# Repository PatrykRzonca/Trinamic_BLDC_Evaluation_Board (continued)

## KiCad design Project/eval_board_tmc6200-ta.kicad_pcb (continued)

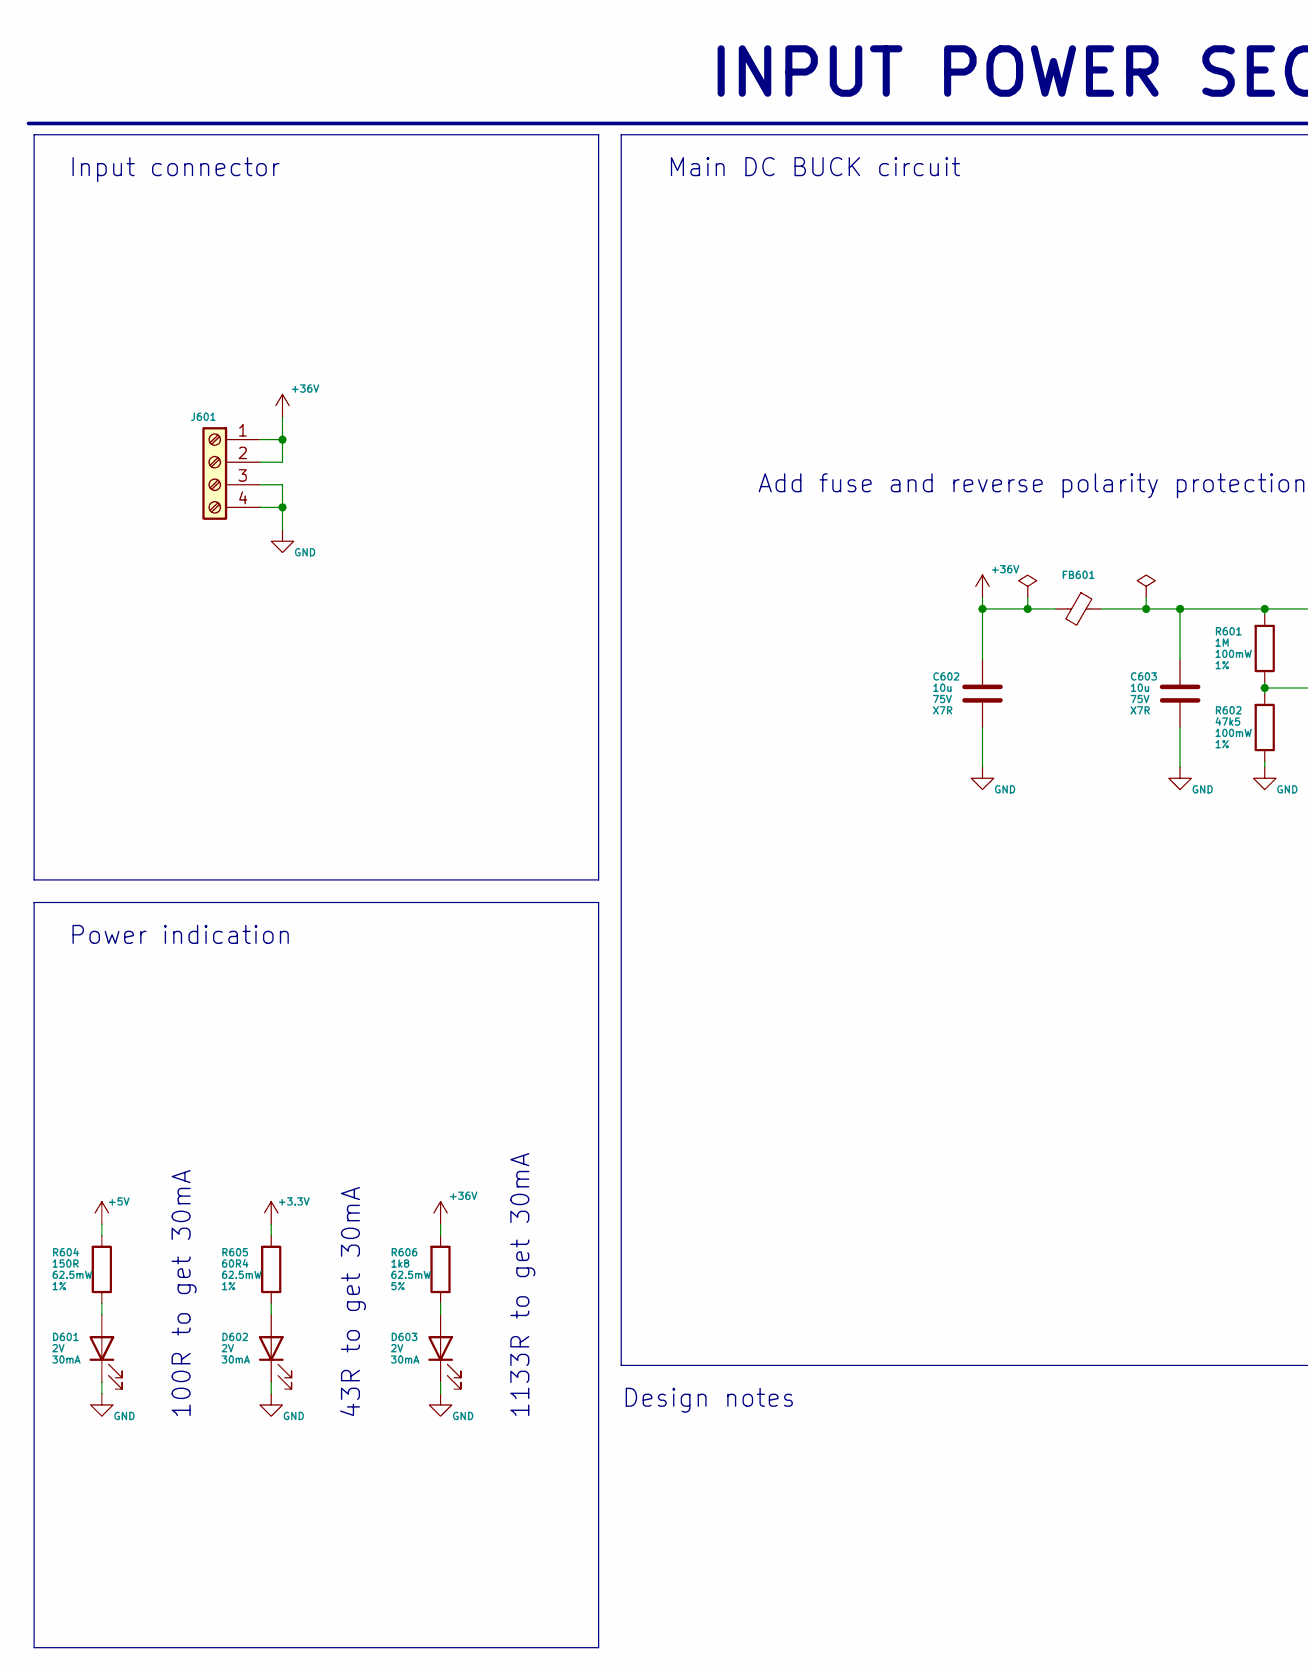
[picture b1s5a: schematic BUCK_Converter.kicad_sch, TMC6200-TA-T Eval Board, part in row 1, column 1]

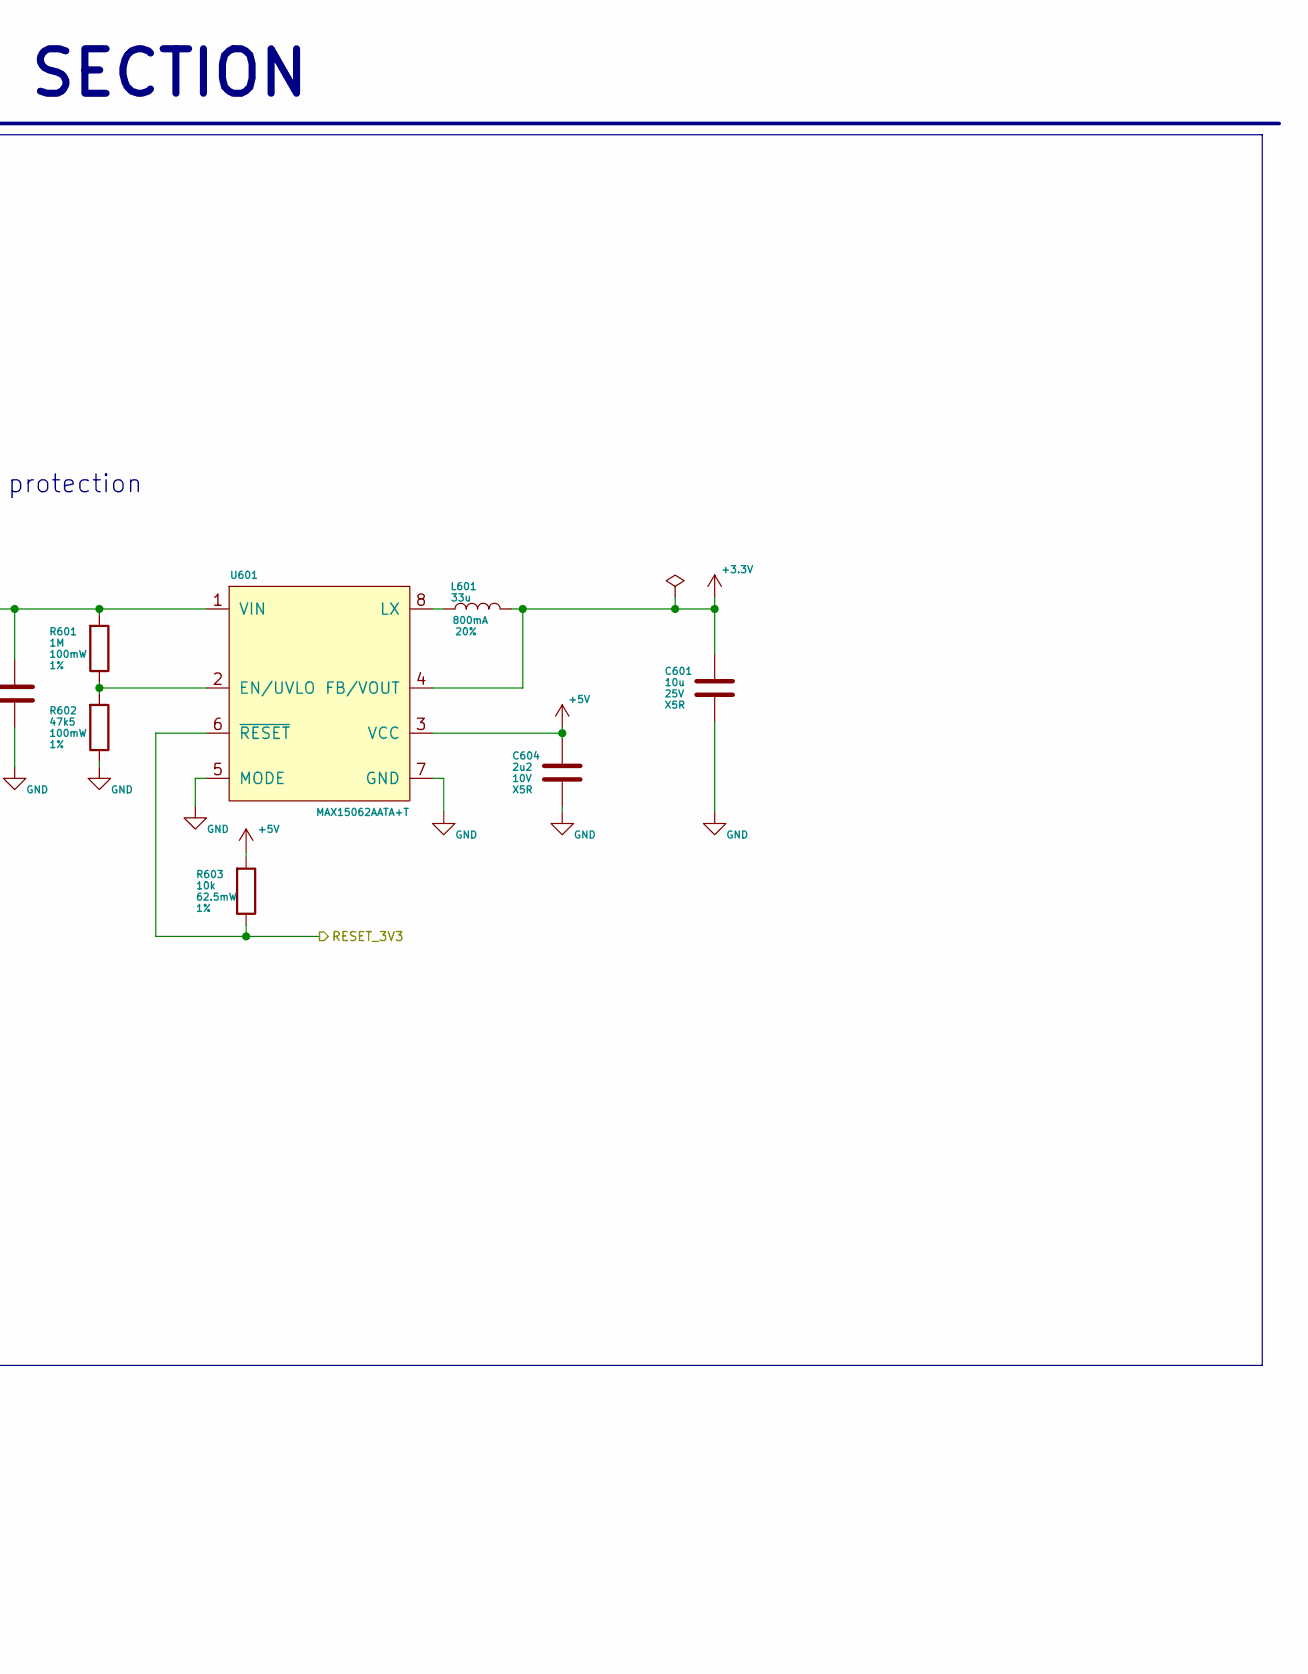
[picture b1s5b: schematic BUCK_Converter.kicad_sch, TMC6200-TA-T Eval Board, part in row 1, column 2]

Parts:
C601: 10u; C_1206_3216Metric; DC Voltage 25V; Tolerance 20%; Part Number CL31A106KAHNNNE
C602, C603: 10u; C_1210_3225Metric; DC Voltage 75V; Tolerance 10%; Part Number C3225X7R1N106K250AC
C604: 2u2; C_0603_1608Metric; DC Voltage 10V; Tolerance 10%; Part Number LMK107BJ225KAHT
D601, D602, D603: LED; D_0402_1005Metric; Forward Voltage 2V; Part Number 150040VS73240
FB601: Ferrite_Bead; R_0603_1608Metric
J601: Screw_Terminal_01x04; PinSocket_1x04_P2.54mm_Vertical
L601: 33u; L_Coilcraft_XAL5030; Tolerance 20%
R601: 1M; R_0603_1608Metric; Tolerance 1%; Voltage 75V; Part Number CRCW06031M00FKEAC
R602: 47k5; R_0603_1608Metric; Tolerance 1%; Voltage 75V; Part Number CRCW060347K5FKEAC
R603: 10k; R_0402_1005Metric; Tolerance 1%; Voltage 50V; Part Number RC0402FR-0710KL
R604: 150R; R_0402_1005Metric; Tolerance 1%; Voltage 50V; Part Number RC0402FR-7D150RL
R605: 60R4; R_0402_1005Metric; Tolerance 1%; Voltage 50V; Part Number RC0402FR-0760R4L
R606: 1k8; R_0402_1005Metric; Tolerance 5%; Voltage 50V; Part Number RC0402JR-071K8L
U601: MAX15062AATA+T; MAX15062AATA+T_TDFN-8

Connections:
+3V3: C601.1, L601.2, R605.2, U601.4 (FB/VOUT); also elsewhere on the board
+5V: C604.1, R603.2, R604.2, U601.3 (VCC); also elsewhere on the board
+36V: C602.1, FB601.2, J601.1, J601.2, R606.2; also elsewhere on the board
/Microcontroller/RESET_3V3: R603.1, U601.6 (~RESET); also elsewhere on the board
GND: C601.2, C602.2, C603.2, C604.2, D601.1 (K), D602.1 (K), D603.1 (K), J601.3, J601.4, R602.1, U601.5 (MODE), U601.7 (GND); also elsewhere on the board
unnamed: C603.1, FB601.1, R601.2, U601.1 (VIN)
unnamed: D601.2 (A), R604.1
unnamed: D602.2 (A), R605.1
unnamed: D603.2 (A), R606.1
unnamed: L601.1, U601.8 (LX)
unnamed: R601.1, R602.2, U601.2 (EN/UVLO)

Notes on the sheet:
1133R to get 30mA
Main DC BUCK circuit
Power indication
Add fuse and reverse polarity protection
Input connector
Design notes
INPUT POWER SECTION
100R to get 30mA
43R to get 30mA

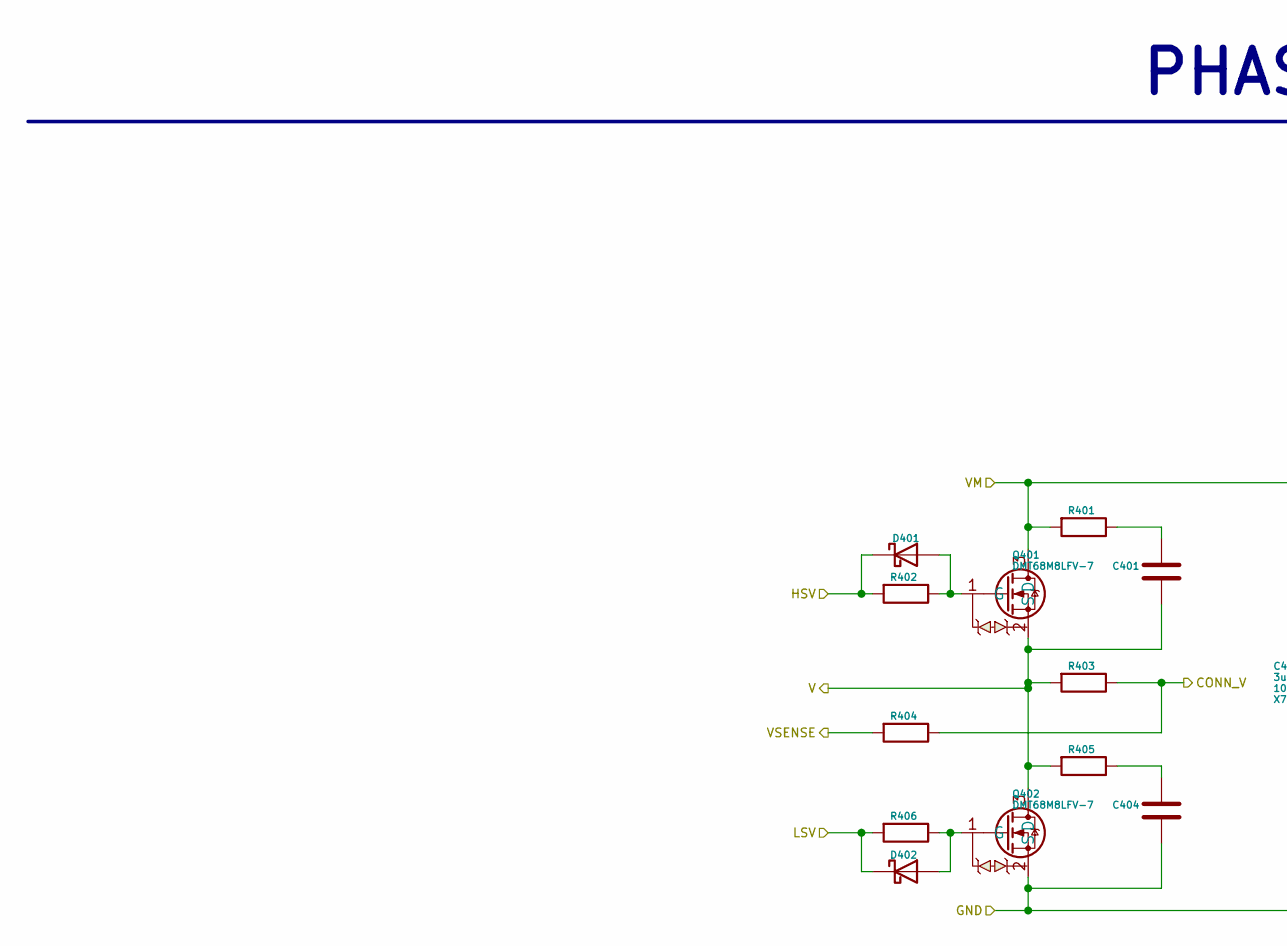
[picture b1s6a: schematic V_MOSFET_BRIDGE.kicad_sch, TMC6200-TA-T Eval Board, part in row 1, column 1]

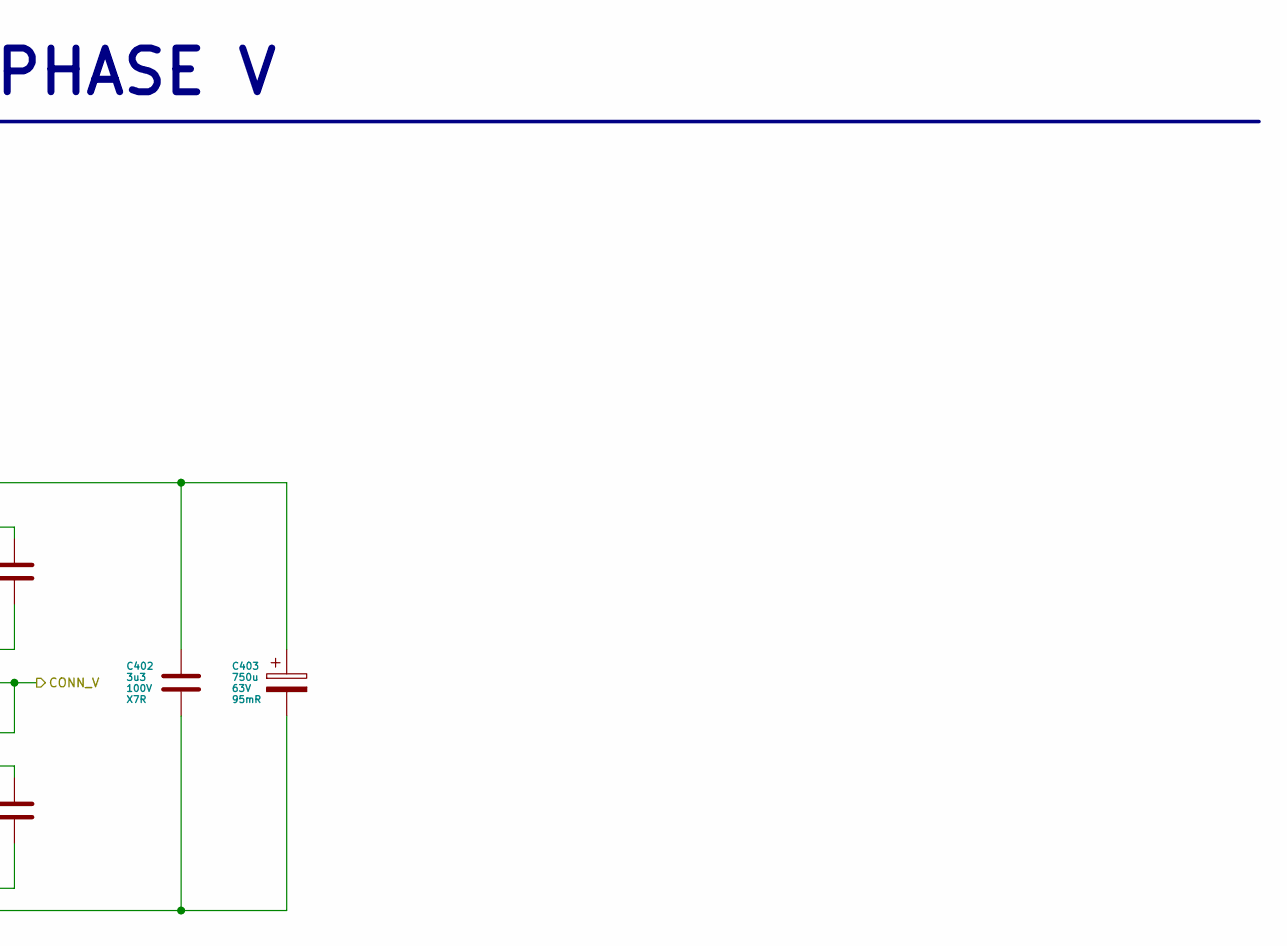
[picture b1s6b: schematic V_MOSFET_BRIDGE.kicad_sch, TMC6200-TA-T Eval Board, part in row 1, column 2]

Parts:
C401, C404: C; C_0402_1005Metric
C402: 3u3; C_1812_4532Metric; DC Voltage 100V; Tolerance 10%; Part Number C1812C335K1RACTU
C403: 750u; CP_Elec_18x17.5; DC Voltage 63V; Tolerance 20%; Part Number EEE-TP1J751V
D401, D402: D_Schottky; D_SOD-123
Q401, Q402: DMT68M8LFV-7; DMT68M8LFV-7_PowerDI5060-8
R401, R402, R404, R405, R406: R; R_0402_1005Metric
R403: R; R_1210_3225Metric

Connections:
+36V: C402.2, C403.1, Q401.3 (D), R401.2; also elsewhere on the board
/BLDC_MOTOR/CONN_V: R403.1, R404.1
/BLDC_MOTOR/HSV: D401.1 (K), R402.2; also elsewhere on the board
/BLDC_MOTOR/LSV: D402.1 (K), R406.2; also elsewhere on the board
/BLDC_MOTOR/V: C401.1, Q401.2 (S), Q402.3 (D), R403.2, R405.2; also elsewhere on the board
/BLDC_MOTOR/VSENSE: R404.2; also elsewhere on the board
GND: C402.1, C403.2, C404.1, Q402.2 (S); also elsewhere on the board
unnamed: C401.2, R401.1
unnamed: C404.2, R405.1
unnamed: D401.2 (A), Q401.1 (G), R402.1
unnamed: D402.2 (A), Q402.1 (G), R406.1

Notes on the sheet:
PHASE V

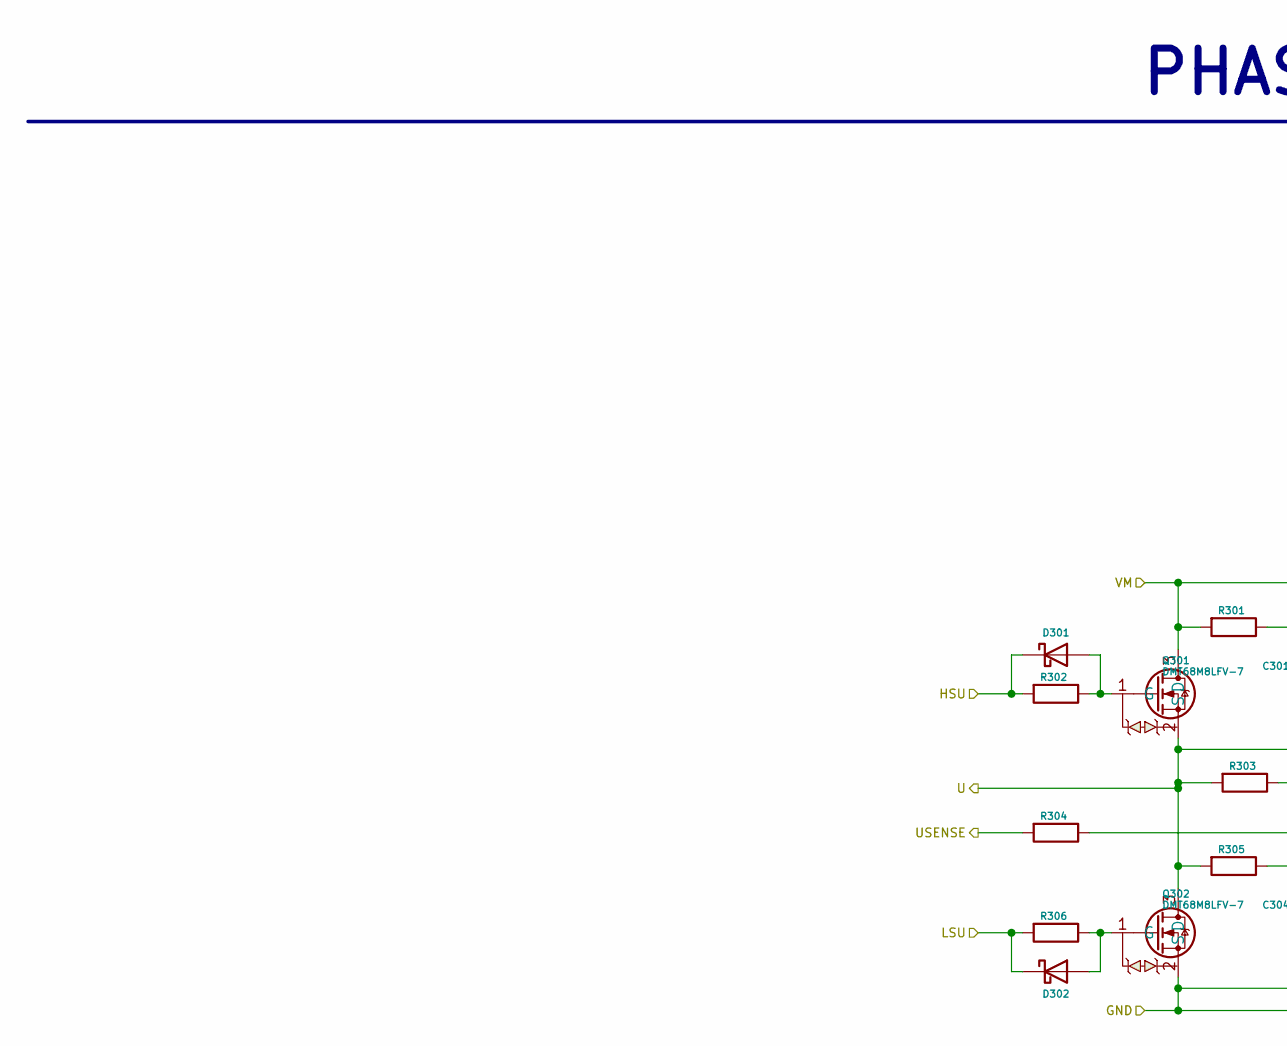
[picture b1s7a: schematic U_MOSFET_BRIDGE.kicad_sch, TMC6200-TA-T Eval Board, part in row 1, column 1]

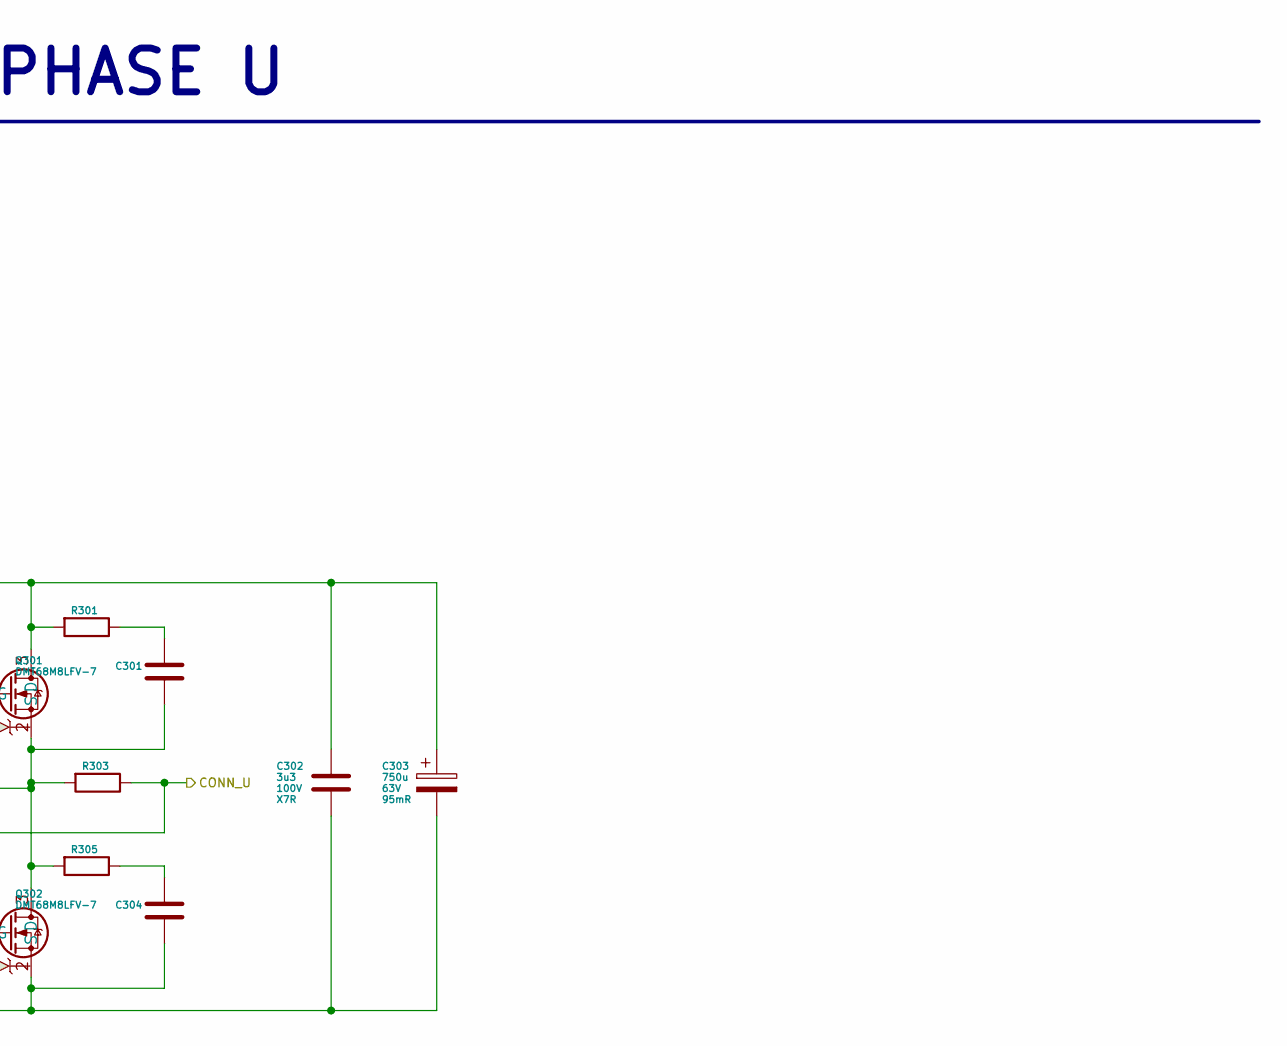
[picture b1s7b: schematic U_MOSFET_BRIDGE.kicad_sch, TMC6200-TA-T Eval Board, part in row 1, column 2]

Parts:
C301, C304: C; C_0402_1005Metric
C302: 3u3; C_1812_4532Metric; DC Voltage 100V; Tolerance 10%; Part Number C1812C335K1RACTU
C303: 750u; CP_Elec_18x17.5; DC Voltage 63V; Tolerance 20%; Part Number EEE-TP1J751V
D301, D302: D_Schottky; D_SOD-123
Q301, Q302: DMT68M8LFV-7; DMT68M8LFV-7_PowerDI5060-8
R301, R302, R304, R305, R306: R; R_0402_1005Metric
R303: R; R_1210_3225Metric

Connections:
+36V: C302.2, C303.1, Q301.3 (D), R301.2; also elsewhere on the board
/BLDC_MOTOR/CONN_U: R303.1, R304.1
/BLDC_MOTOR/HSU: D301.1 (K), R302.2; also elsewhere on the board
/BLDC_MOTOR/LSU: D302.1 (K), R306.2; also elsewhere on the board
/BLDC_MOTOR/U: C301.1, Q301.2 (S), Q302.3 (D), R303.2, R305.2; also elsewhere on the board
/BLDC_MOTOR/USENSE: R304.2; also elsewhere on the board
GND: C302.1, C303.2, C304.1, Q302.2 (S); also elsewhere on the board
unnamed: C301.2, R301.1
unnamed: C304.2, R305.1
unnamed: D301.2 (A), Q301.1 (G), R302.1
unnamed: D302.2 (A), Q302.1 (G), R306.1

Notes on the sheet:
PHASE U

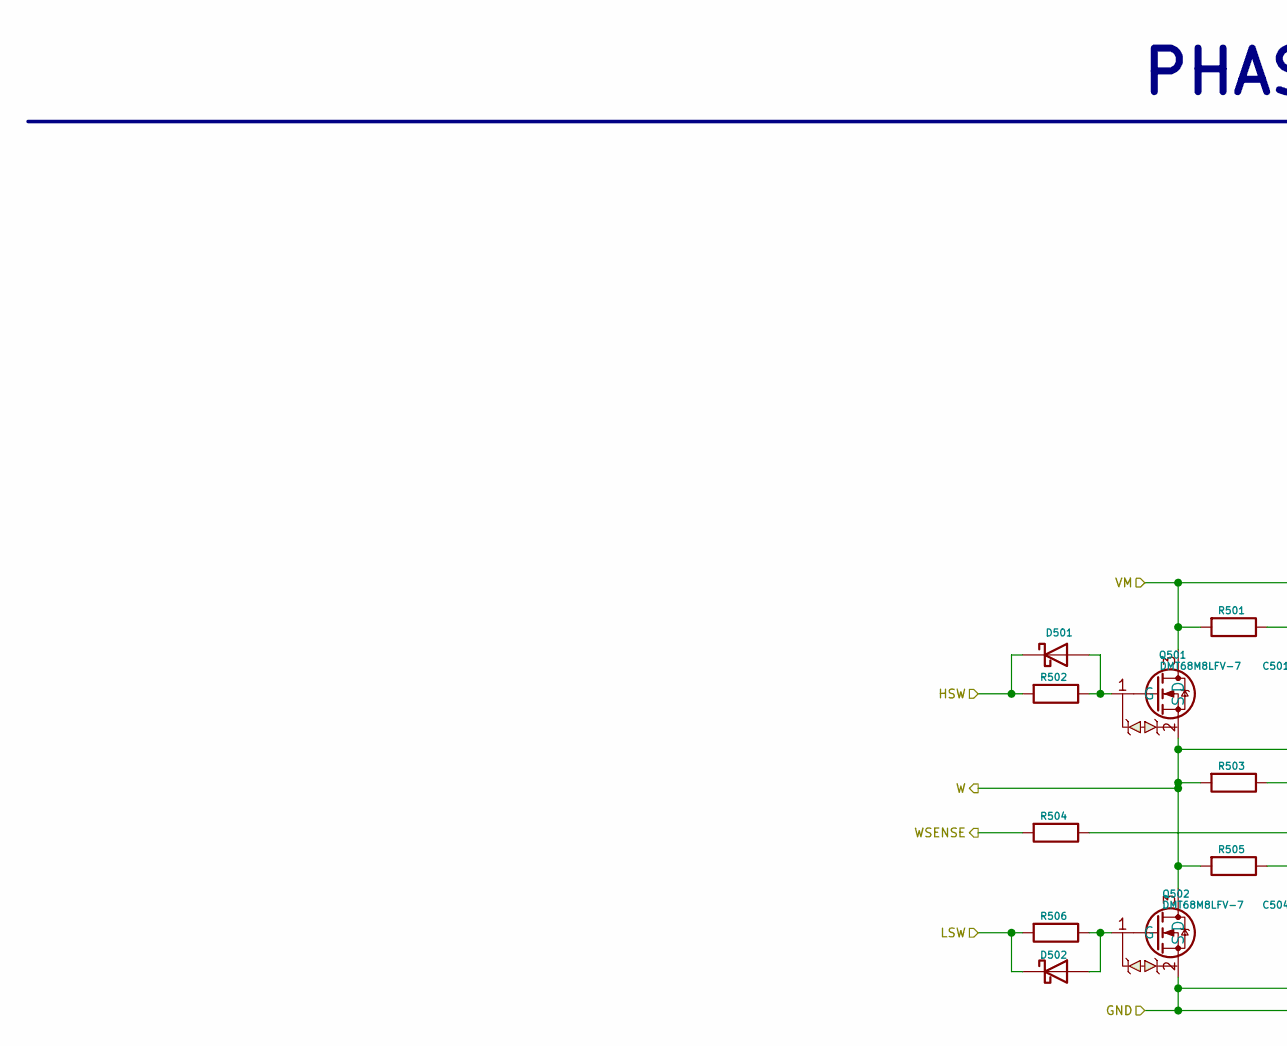
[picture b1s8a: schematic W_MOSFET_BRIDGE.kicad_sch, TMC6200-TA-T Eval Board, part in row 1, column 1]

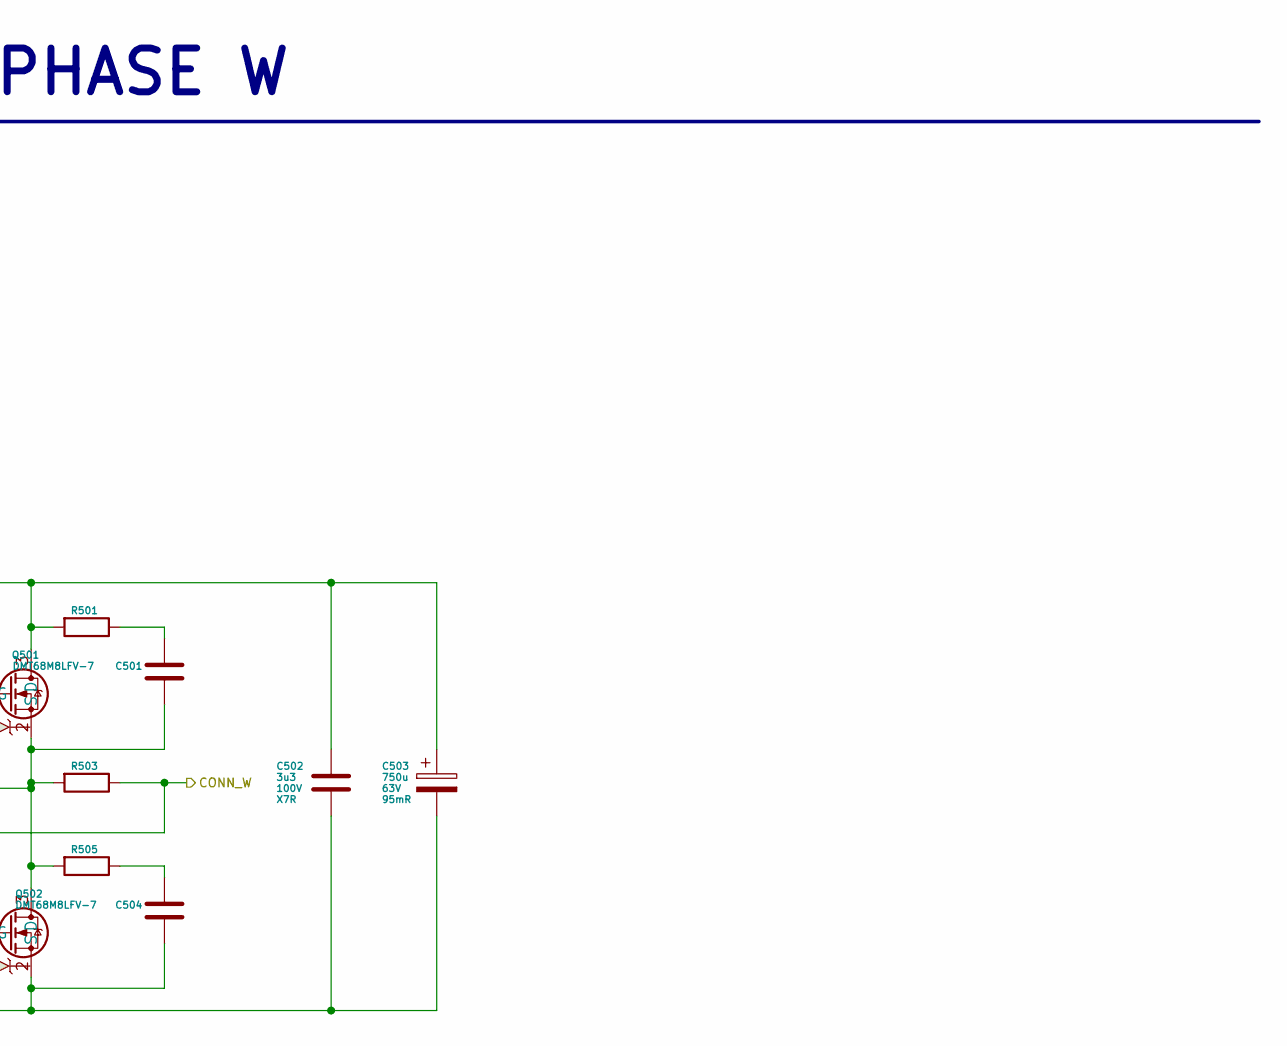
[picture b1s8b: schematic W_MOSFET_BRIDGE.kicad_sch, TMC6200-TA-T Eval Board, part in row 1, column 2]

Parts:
C501, C504: C; C_0402_1005Metric
C502: 3u3; C_1812_4532Metric; DC Voltage 100V; Tolerance 10%; Part Number C1812C335K1RACTU
C503: 750u; CP_Elec_18x17.5; DC Voltage 63V; Tolerance 20%; Part Number EEE-TP1J751V
D501, D502: D_Schottky; D_SOD-123
Q501, Q502: DMT68M8LFV-7; DMT68M8LFV-7_PowerDI5060-8
R501, R502, R504, R505, R506: R; R_0402_1005Metric
R503: R; R_1210_3225Metric

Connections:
+36V: C502.2, C503.1, Q501.3 (D), R501.2; also elsewhere on the board
/BLDC_MOTOR/CONN_W: R503.1, R504.1
/BLDC_MOTOR/HSW: D501.1 (K), R502.2; also elsewhere on the board
/BLDC_MOTOR/LSW: D502.1 (K), R506.2; also elsewhere on the board
/BLDC_MOTOR/W: C501.1, Q501.2 (S), Q502.3 (D), R503.2, R505.2; also elsewhere on the board
/BLDC_MOTOR/WSENSE: R504.2; also elsewhere on the board
GND: C502.1, C503.2, C504.1, Q502.2 (S); also elsewhere on the board
unnamed: C501.2, R501.1
unnamed: C504.2, R505.1
unnamed: D501.2 (A), Q501.1 (G), R502.1
unnamed: D502.2 (A), Q502.1 (G), R506.1

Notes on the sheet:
PHASE W

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
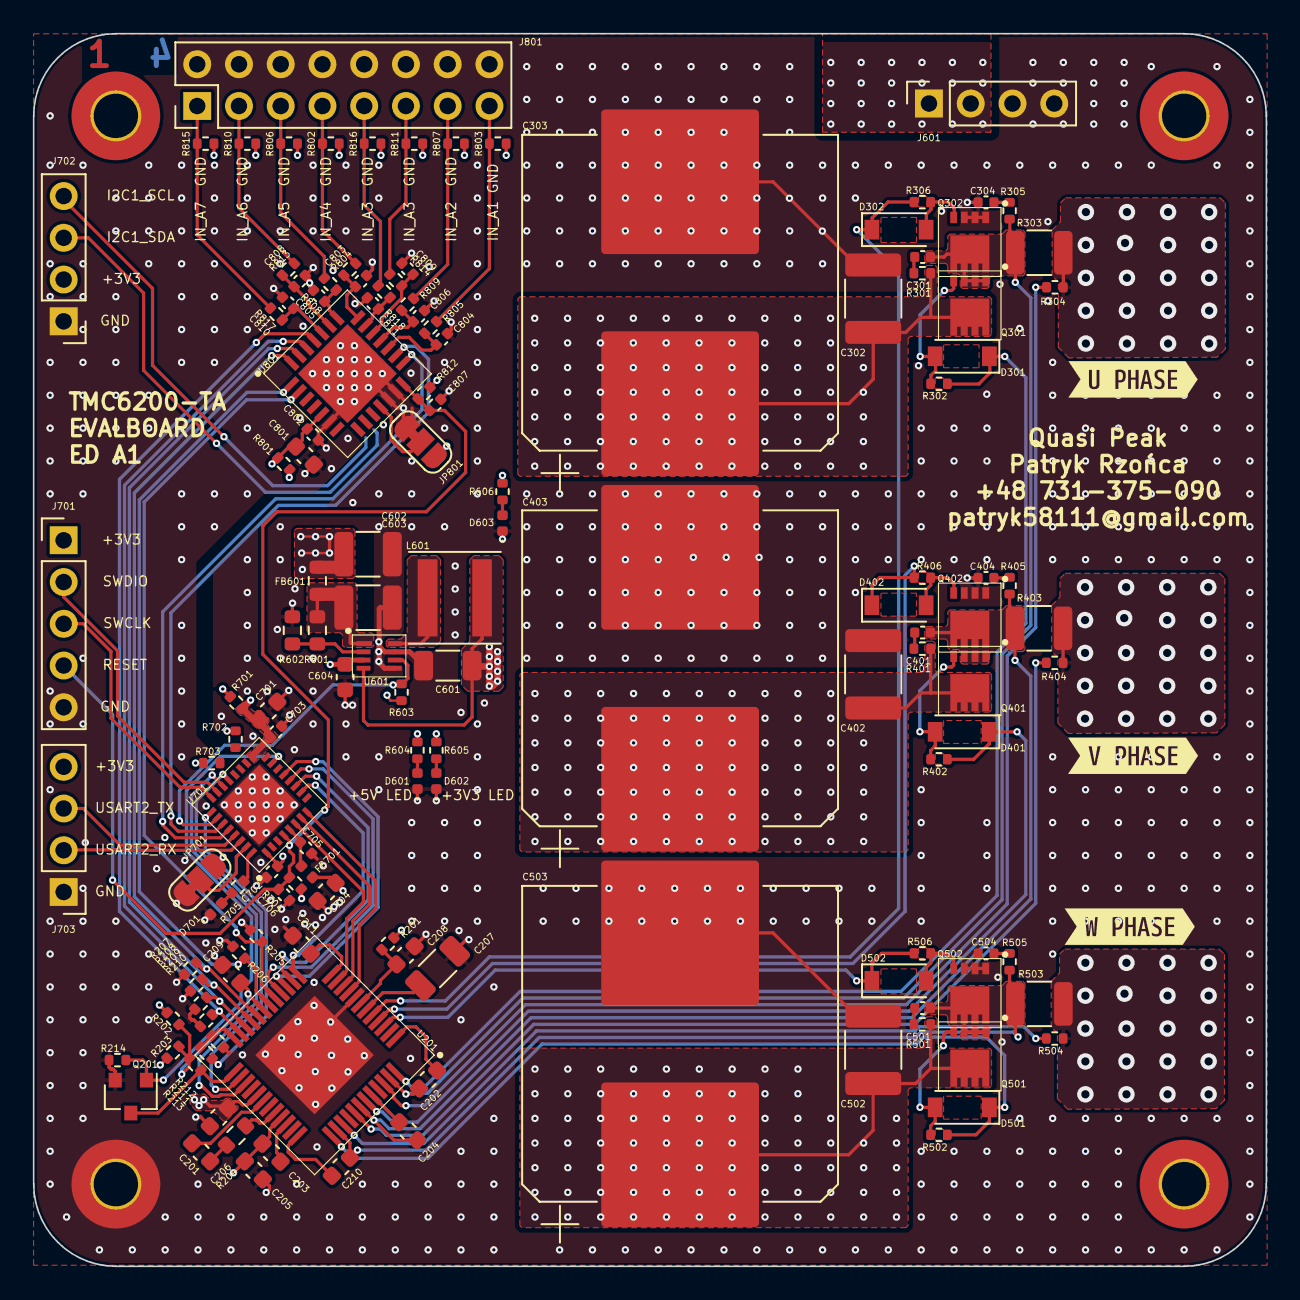
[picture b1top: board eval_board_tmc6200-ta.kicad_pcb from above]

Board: 4 copper layers, 75.0 x 75.0 mm, 143 parts (0 on the bottom side), 100 nets.

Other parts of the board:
kibuzzard-623F17B5: G***; kibuzzard-623F17B5
kibuzzard-623F17D6: G***; kibuzzard-623F17D6
kibuzzard-623F17E7: G***; kibuzzard-623F17E7

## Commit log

2022-03-27 First commit for this project
2022-03-27 More files cleanup for this project
2022-03-27 Printed schematic into pdf file.
2022-03-27 More files cleanup
2022-03-27 Further project cleanup, added datasheets, generated BOM files and 3D shape of a board
2022-03-30 Cleanup ED A1 version
2022-04-02 Cleaning files, added testpoints
